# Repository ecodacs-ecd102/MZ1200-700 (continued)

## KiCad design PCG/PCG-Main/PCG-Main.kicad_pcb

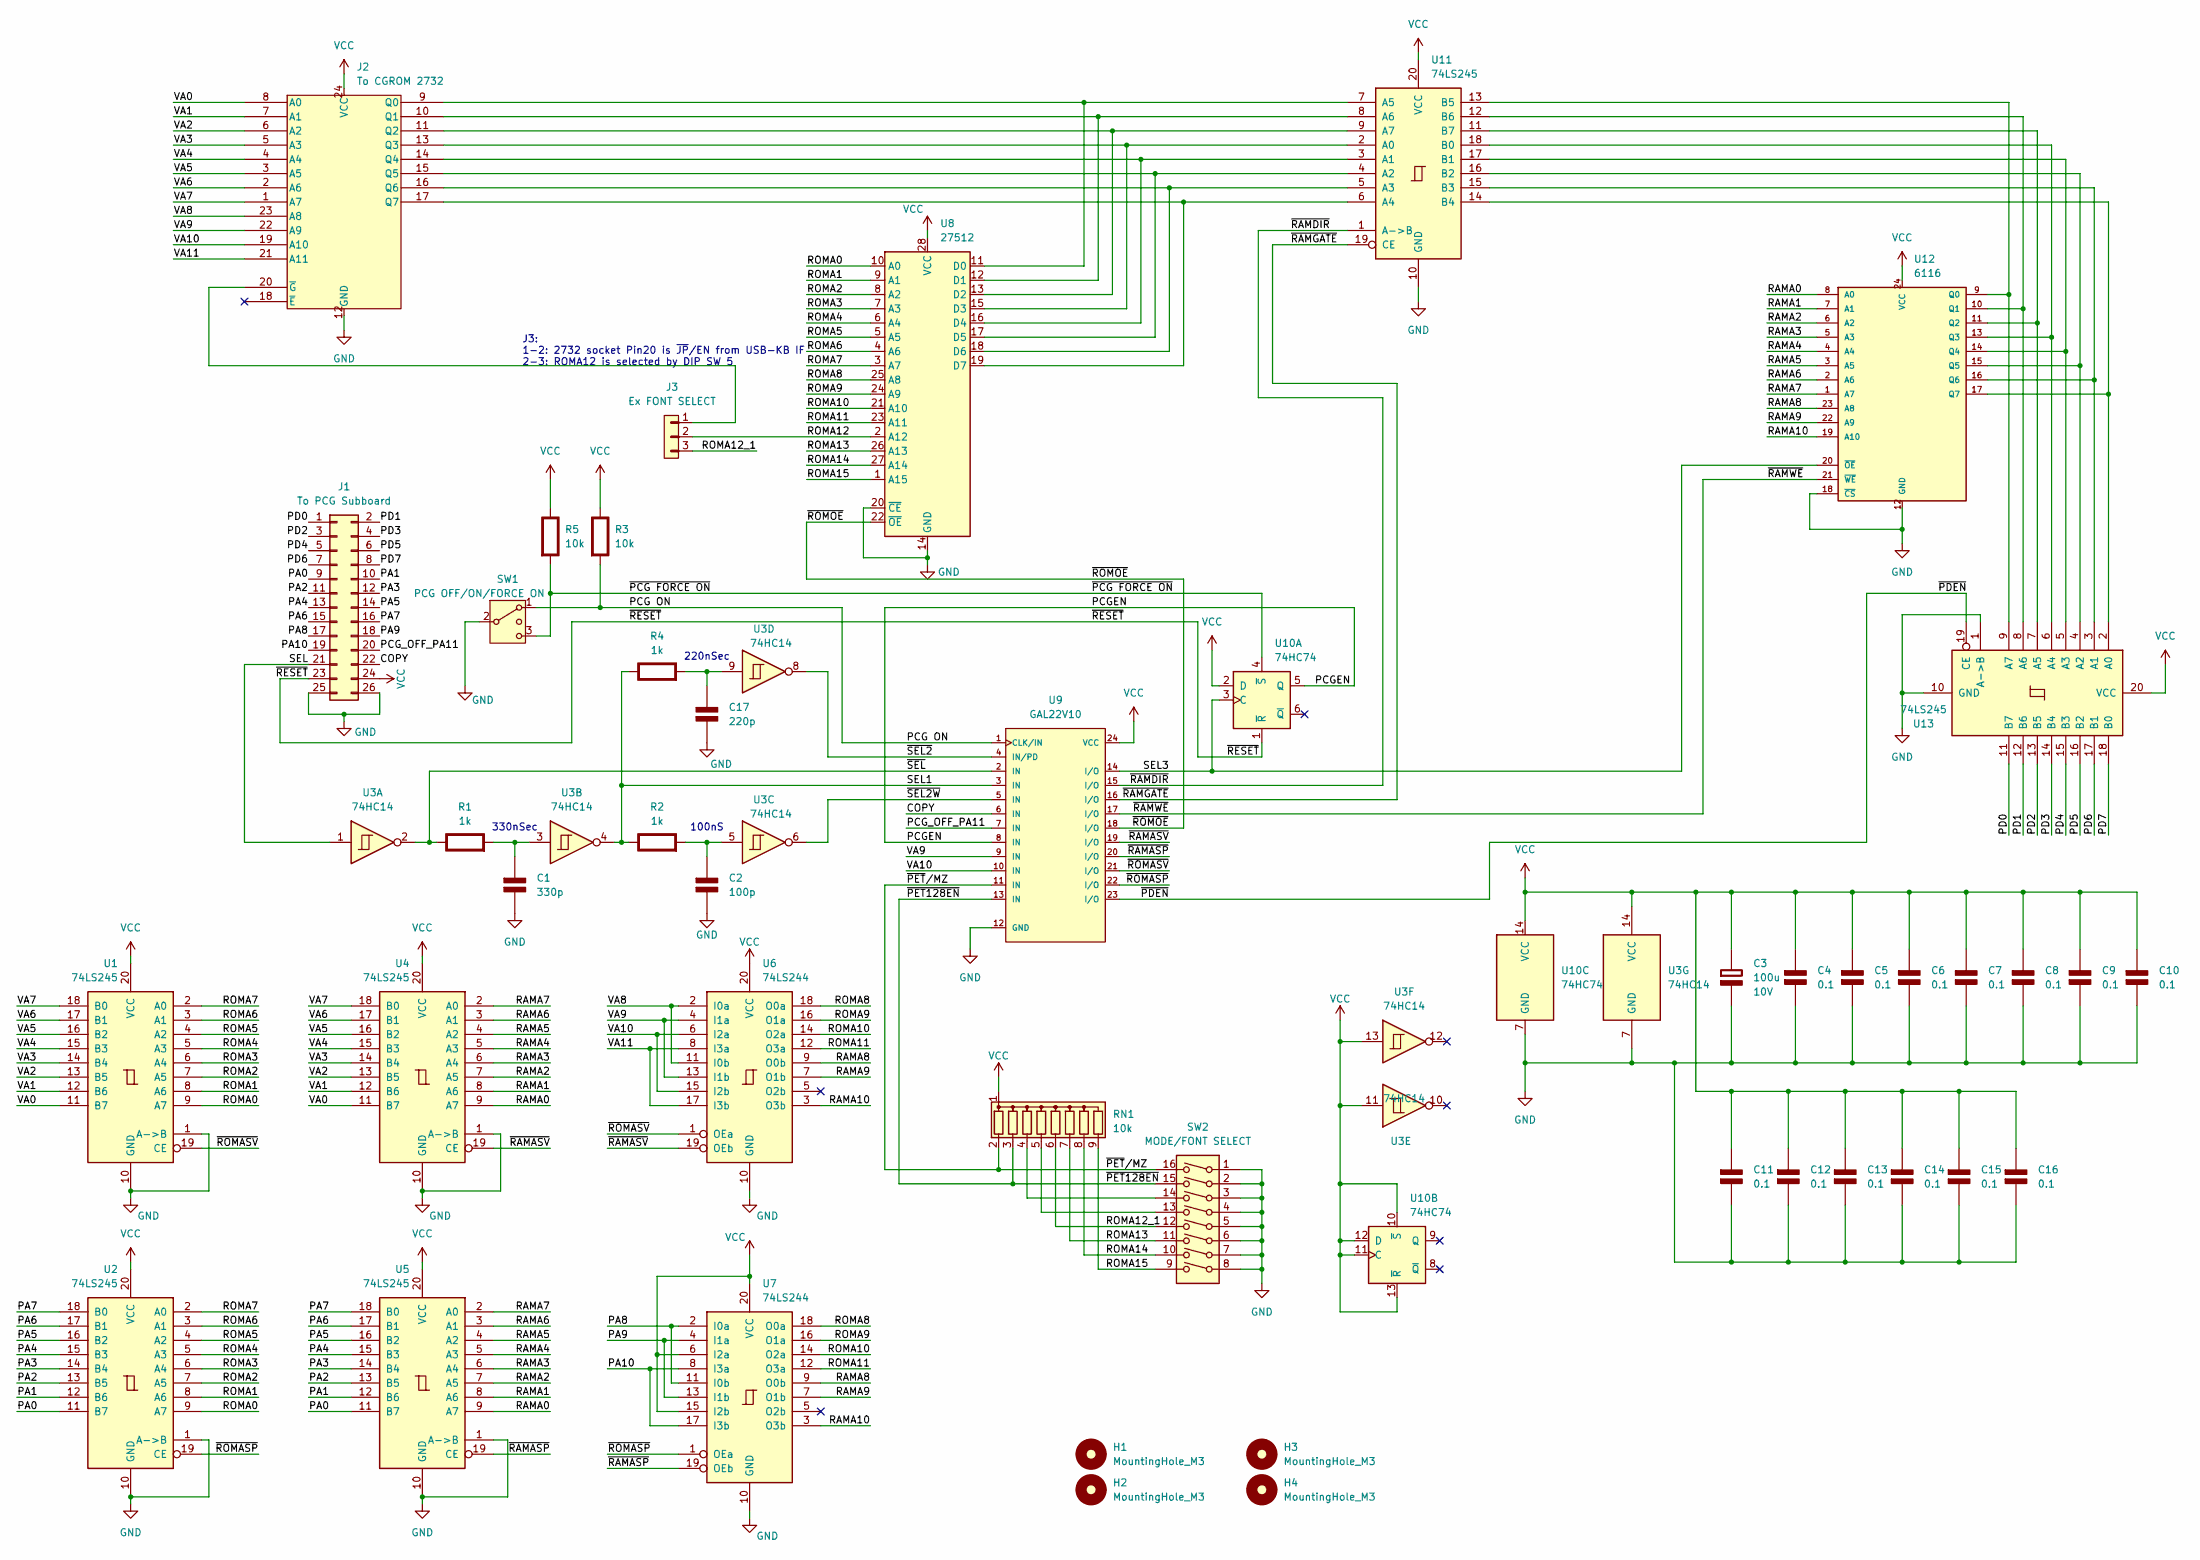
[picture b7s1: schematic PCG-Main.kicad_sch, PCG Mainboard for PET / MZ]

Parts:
C1: 330p; LargePad_R_Axial_DIN0204_L3.6mm_D1.6mm_P2.54mm_Vertical; Rating V
C2: 100p; LargePad_R_Axial_DIN0204_L3.6mm_D1.6mm_P2.54mm_Vertical; Rating V
C3: 100u; CP_Radial_D8.0mm_P3.50mm; Rating 10V
C4, C5, C6, C7, C8, C9, C10, C11, C12, C13, C14, C15, C16: 0.1; LargePad_R_Axial_DIN0204_L3.6mm_D1.6mm_P2.54mm_Vertical; Rating V
C17: 220p; LargePad_R_Axial_DIN0204_L3.6mm_D1.6mm_P2.54mm_Vertical; Rating V
H1, H2, H3, H4: MountingHole_M3; MountingHole_3.2mm_M3
J1: To PCG Subboard; PinSocket_2x13_P2.54mm_Vertical_LargePad
J2: To CGROM 2732; DIP-24_W15.24mm_Socket_LongPads
J3: Ex FONT SELECT; PinHeader_1x03_P2.54mm_Vertical
R1, R2, R4: 1k; LargePad_R_Axial_DIN0207_L6.3mm_D2.5mm_P7.62mm_Horizontal; Rating W
R3, R5: 10k; LargePad_R_Axial_DIN0207_L6.3mm_D2.5mm_P7.62mm_Horizontal; Rating W
RN1: 10k; R_Array_SIP9
SW1: PCG OFF/ON/FORCE ON; PinHeader_1x03_P2.54mm_Vertical
SW2: MODE/FONT SELECT; DIP-16_W7.62mm_Socket_LongPads
U1, U2, U4, U5, U11, U13: 74LS245; DIP-20_W7.62mm_Socket_LongPads
U3: 74HC14; DIP-14_W7.62mm_Socket_LongPads
U6, U7: 74LS244; DIP-20_W7.62mm_Socket_LongPads
U8: 27512; DIP-28_W15.24mm_Socket_LongPads
U9: GAL22V10; DIP-24_W7.62mm_Socket_LongPads
U10: 74HC74; DIP-14_W7.62mm_Socket_LongPads
U12: 6116; DIP-24_W15.24mm_Socket_LongPads

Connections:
/COPY: J1.22, U9.6 (IN)
/PA0: J1.9, U2.11 (B7), U5.11 (B7)
/PA1: J1.10, U2.12 (B6), U5.12 (B6)
/PA2: J1.11, U2.13 (B5), U5.13 (B5)
/PA3: J1.12, U2.14 (B4), U5.14 (B4)
/PA4: J1.13, U2.15 (B3), U5.15 (B3)
/PA5: J1.14, U2.16 (B2), U5.16 (B2)
/PA6: J1.15, U2.17 (B1), U5.17 (B1)
/PA7: J1.16, U2.18 (B0), U5.18 (B0)
/PA8: J1.17, U7.2 (I0a), U7.11 (I0b)
/PA9: J1.18, U7.4 (I1a), U7.13 (I1b)
/PA10: J1.19, U7.8 (I3a), U7.17 (I3b)
/PCG ON: R3.2 (-), SW1.1, U9.1 (CLK/IN)
/PCGEN: U9.8 (IN), U10.5 (Q)
/PCG_OFF_PA11: J1.20, U9.7 (IN)
/PD0: J1.1, U13.11 (B7)
/PD1: J1.2, U13.12 (B6)
/PD2: J1.3, U13.13 (B5)
/PD3: J1.4, U13.14 (B4)
/PD4: J1.5, U13.15 (B3)
/PD5: J1.6, U13.16 (B2)
/PD6: J1.7, U13.17 (B1)
/PD7: J1.8, U13.18 (B0)
/RAMA0: U4.9 (A7), U5.9 (A7), U12.8 (A0)
/RAMA1: U4.8 (A6), U5.8 (A6), U12.7 (A1)
/RAMA2: U4.7 (A5), U5.7 (A5), U12.6 (A2)
/RAMA3: U4.6 (A4), U5.6 (A4), U12.5 (A3)
/RAMA4: U4.5 (A3), U5.5 (A3), U12.4 (A4)
/RAMA5: U4.4 (A2), U5.4 (A2), U12.3 (A5)
/RAMA6: U4.3 (A1), U5.3 (A1), U12.2 (A6)
/RAMA7: U4.2 (A0), U5.2 (A0), U12.1 (A7)
/RAMA8: U6.9 (O0b), U7.9 (O0b), U12.23 (A8)
/RAMA9: U6.7 (O1b), U7.7 (O1b), U12.22 (A9)
/RAMA10: U6.3 (O3b), U7.3 (O3b), U12.19 (A10)
/ROMA0: U1.9 (A7), U2.9 (A7), U8.10 (A0)
/ROMA1: U1.8 (A6), U2.8 (A6), U8.9 (A1)
/ROMA2: U1.7 (A5), U2.7 (A5), U8.8 (A2)
/ROMA3: U1.6 (A4), U2.6 (A4), U8.7 (A3)
/ROMA4: U1.5 (A3), U2.5 (A3), U8.6 (A4)
/ROMA5: U1.4 (A2), U2.4 (A2), U8.5 (A5)
/ROMA6: U1.3 (A1), U2.3 (A1), U8.4 (A6)
/ROMA7: U1.2 (A0), U2.2 (A0), U8.3 (A7)
/ROMA8: U6.18 (O0a), U7.18 (O0a), U8.25 (A8)
/ROMA9: U6.16 (O1a), U7.16 (O1a), U8.24 (A9)
/ROMA10: U6.14 (O2a), U7.14 (O2a), U8.21 (A10)
/ROMA11: U6.12 (O3a), U7.12 (O3a), U8.23 (A11)
/ROMA12: J3.2, U8.2 (A12)
/ROMA12_1: J3.3, RN1.6 (R5), SW2.12
/ROMA13: RN1.7 (R6), SW2.11, U8.26 (A13)
/ROMA14: RN1.8 (R7), SW2.10, U8.27 (A14)
/ROMA15: RN1.9 (R8), SW2.9, U8.1 (A15)
/SEL: J1.21, U3.1
/SEL1: R2.1 (+), R4.1 (+), U3.4, U9.3 (IN)
/SEL3: U9.14 (I/O), U10.3 (C), U12.20 (~OE)
/VA0: J2.8 (A0), U1.11 (B7), U4.11 (B7)
/VA1: J2.7 (A1), U1.12 (B6), U4.12 (B6)
/VA2: J2.6 (A2), U1.13 (B5), U4.13 (B5)
/VA3: J2.5 (A3), U1.14 (B4), U4.14 (B4)
/VA4: J2.4 (A4), U1.15 (B3), U4.15 (B3)
/VA5: J2.3 (A5), U1.16 (B2), U4.16 (B2)
/VA6: J2.2 (A6), U1.17 (B1), U4.17 (B1)
/VA7: J2.1 (A7), U1.18 (B0), U4.18 (B0)
/VA8: J2.23 (A8), U6.2 (I0a), U6.11 (I0b)
/VA9: J2.22 (A9), U6.4 (I1a), U6.13 (I1b), U9.9 (IN)
/VA10: J2.19 (A10), U6.6 (I2a), U6.15 (I2b), U9.10 (IN)
/VA11: J2.21 (A11), U6.8 (I3a), U6.17 (I3b)
/~PCG FORCE ON: R5.2 (-), SW1.3 (4), U10.4 (~S)
/~PDEN: U9.23 (I/O), U13.19 (CE)
/~PET128EN: RN1.3 (R2), SW2.15, U9.13 (IN)
/~PET/MZ: RN1.2 (R1), SW2.16, U9.11 (IN)
/~RAMASP: U5.19 (CE), U7.19 (OEb), U9.20 (I/O)
/~RAMASV: U4.19 (CE), U6.19 (OEb), U9.19 (I/O)
/~RAMDIR: U9.15 (I/O), U11.1 (A->B)
/~RAMGATE: U9.16 (I/O), U11.19 (CE)
/~RAMWE: U9.17 (I/O), U12.21 (~WE)
/~RESET: J1.23, U10.1 (~R)
/~ROMASP: U2.19 (CE), U7.1 (OEa), U9.22 (I/O)
/~ROMASV: U1.19 (CE), U6.1 (OEa), U9.21 (I/O)
/~ROMOE: U8.22 (~OE), U9.18 (I/O)
/~SEL2W: U3.6, U9.5 (IN)
/~SEL2: U3.8, U9.4 (IN/PD)
/~SEL: R1.1 (+), U3.2, U9.2 (IN)
GND: C1.2 (-), C2.2 (-), C3.2 (-), C4.2 (-), C5.2 (-), C6.2 (-), C7.2 (-), C8.2 (-), C9.2 (-), C10.2 (-), C11.2 (-), C12.2 (-), C13.2 (-), C14.2 (-), C15.2 (-), C16.2 (-), C17.2 (-), J1.25, J1.26, J2.12 (GND), SW1.2 (3), SW2.1, SW2.2, SW2.3, SW2.4, SW2.5, SW2.6, SW2.7, SW2.8, U1.1 (A->B), U1.10 (GND), U2.1 (A->B), U2.10 (GND), U3.7 (GND), U4.1 (A->B), U4.10 (GND), U5.1 (A->B), U5.10 (GND), U6.10 (GND), U7.10 (GND), U8.14 (GND), U8.20 (~CE), U9.12 (GND), U10.7 (GND), U11.10 (GND), U12.12 (GND), U12.18 (~CS), U13.1 (A->B), U13.10 (GND)
unnamed: C1.1 (+), R1.2 (-), U3.3
unnamed: C2.1 (+), R2.2 (-), U3.5
unnamed: C17.1 (+), R4.2 (-), U3.9
unnamed: J2.9 (Q0), U8.11 (D0), U11.7 (A5)
unnamed: J2.10 (Q1), U8.12 (D1), U11.8 (A6)
unnamed: J2.11 (Q2), U8.13 (D2), U11.9 (A7)
unnamed: J2.13 (Q3), U8.15 (D3), U11.2 (A0)
unnamed: J2.14 (Q4), U8.16 (D4), U11.3 (A1)
unnamed: J2.15 (Q5), U8.17 (D5), U11.4 (A2)
unnamed: J2.16 (Q6), U8.18 (D6), U11.5 (A3)
unnamed: J2.17 (Q7), U8.19 (D7), U11.6 (A4)
unnamed: J2.20 (~G), J3.1
unnamed: RN1.4 (R3), SW2.14
unnamed: RN1.5 (R4), SW2.13
unnamed: U11.18 (B0), U12.13 (Q3), U13.6 (A4)
unnamed: U11.17 (B1), U12.14 (Q4), U13.5 (A3)
unnamed: U11.16 (B2), U12.15 (Q5), U13.4 (A2)
unnamed: U11.15 (B3), U12.16 (Q6), U13.3 (A1)
unnamed: U11.14 (B4), U12.17 (Q7), U13.2 (A0)
unnamed: U11.13 (B5), U12.9 (Q0), U13.9 (A7)
unnamed: U11.12 (B6), U12.10 (Q1), U13.8 (A6)
unnamed: U11.11 (B7), U12.11 (Q2), U13.7 (A5)
VCC: C3.1 (+), C4.1 (+), C5.1 (+), C6.1 (+), C7.1 (+), C8.1 (+), C9.1 (+), C10.1 (+), C11.1 (+), C12.1 (+), C13.1 (+), C14.1 (+), C15.1 (+), C16.1 (+), J1.24, J2.24 (VCC), R3.1 (+), R5.1 (+), RN1.1 (common), U1.20 (VCC), U2.20 (VCC), U3.11, U3.13, U3.14 (VCC), U4.20 (VCC), U5.20 (VCC), U6.20 (VCC), U7.6 (I2a), U7.15 (I2b), U7.20 (VCC), U8.28 (VCC), U9.24 (VCC), U10.2 (D), U10.10 (~S), U10.11 (C), U10.12 (D), U10.13 (~R), U10.14 (VCC), U11.20 (VCC), U12.24 (VCC), U13.20 (VCC)

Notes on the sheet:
100nS
J3: 1-2: 2732 socket Pin20 is ~{JP}/EN from USB-KB IF 2-3: ROMA12 is selected by DIP SW 5
220nSec
330nSec

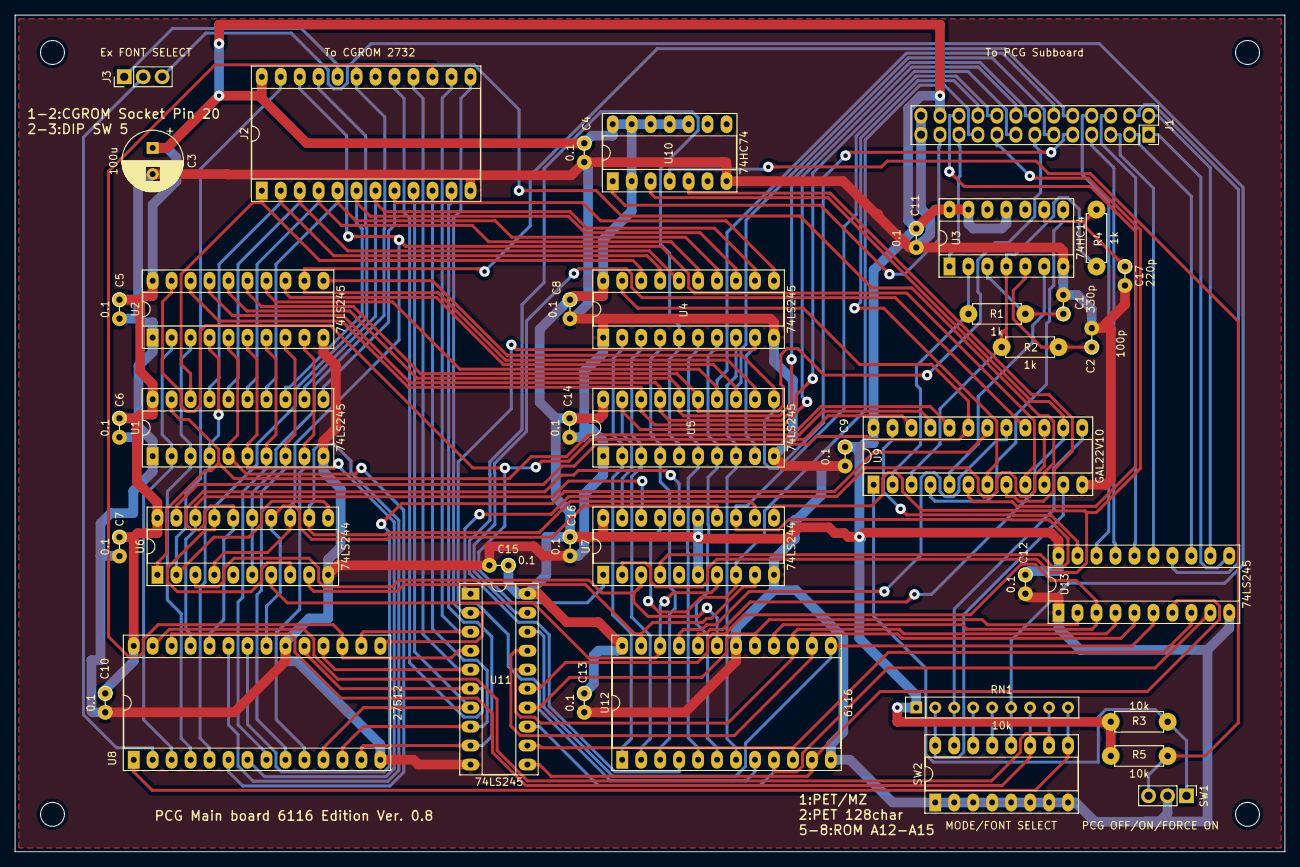
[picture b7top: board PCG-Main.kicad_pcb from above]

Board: 2 copper layers, 170.0 x 112.0 mm, 45 parts (0 on the bottom side), 106 nets.

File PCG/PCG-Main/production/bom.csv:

Designator,Footprint,Quantity,Value,LCSC Part #
C1,LargePad_R_Axial_DIN0204_L3.6mm_D1.6mm_P2.54mm_Vertical,1,330p,
"C10, C11, C12, C13, C14, C15, C16, C4, C5, C6, C7, C8, C9",LargePad_R_Axial_DIN0204_L3.6mm_D1.6mm_P2.54mm_Vertical,13,0.1,
C17,LargePad_R_Axial_DIN0204_L3.6mm_D1.6mm_P2.54mm_Vertical,1,220p,
C2,LargePad_R_Axial_DIN0204_L3.6mm_D1.6mm_P2.54mm_Vertical,1,100p,
C3,CP_Radial_D8.0mm_P3.50mm,1,100u,
"H1, H2, H3, H4",MountingHole_3.2mm_M3,4,MountingHole_M3,
J1,PinSocket_2x13_P2.54mm_Vertical_LargePad,1,To PCG Subboard,
J2,DIP-24_W15.24mm_Socket_LongPads,1,To CGROM 2732,
J3,PinHeader_1x03_P2.54mm_Vertical,1,Ex FONT SELECT,
"R1, R2, R4",LargePad_R_Axial_DIN0207_L6.3mm_D2.5mm_P7.62mm_Horizontal,3,1k,
"R3, R5",LargePad_R_Axial_DIN0207_L6.3mm_D2.5mm_P7.62mm_Horizontal,2,10k,
RN1,R_Array_SIP9,1,10k,
SW1,PinHeader_1x03_P2.54mm_Vertical,1,PCG OFF/ON/FORCE ON,
SW2,DIP-16_W7.62mm_Socket_LongPads,1,MODE/FONT SELECT,
"U1, U11, U13, U2, U4, U5",DIP-20_W7.62mm_Socket_LongPads,6,74HC245,
U10,DIP-14_W7.62mm_Socket_LongPads,1,74HC74,
U12,DIP-24_W15.24mm_Socket_LongPads,1,6116,
U3,DIP-14_W7.62mm_Socket_LongPads,1,74HC14,
"U6, U7",DIP-20_W7.62mm_Socket_LongPads,2,74HC244,
U8,DIP-28_W15.24mm_Socket_LongPads,1,27512,
U9,DIP-24_W7.62mm_Socket_LongPads,1,GAL22V10,

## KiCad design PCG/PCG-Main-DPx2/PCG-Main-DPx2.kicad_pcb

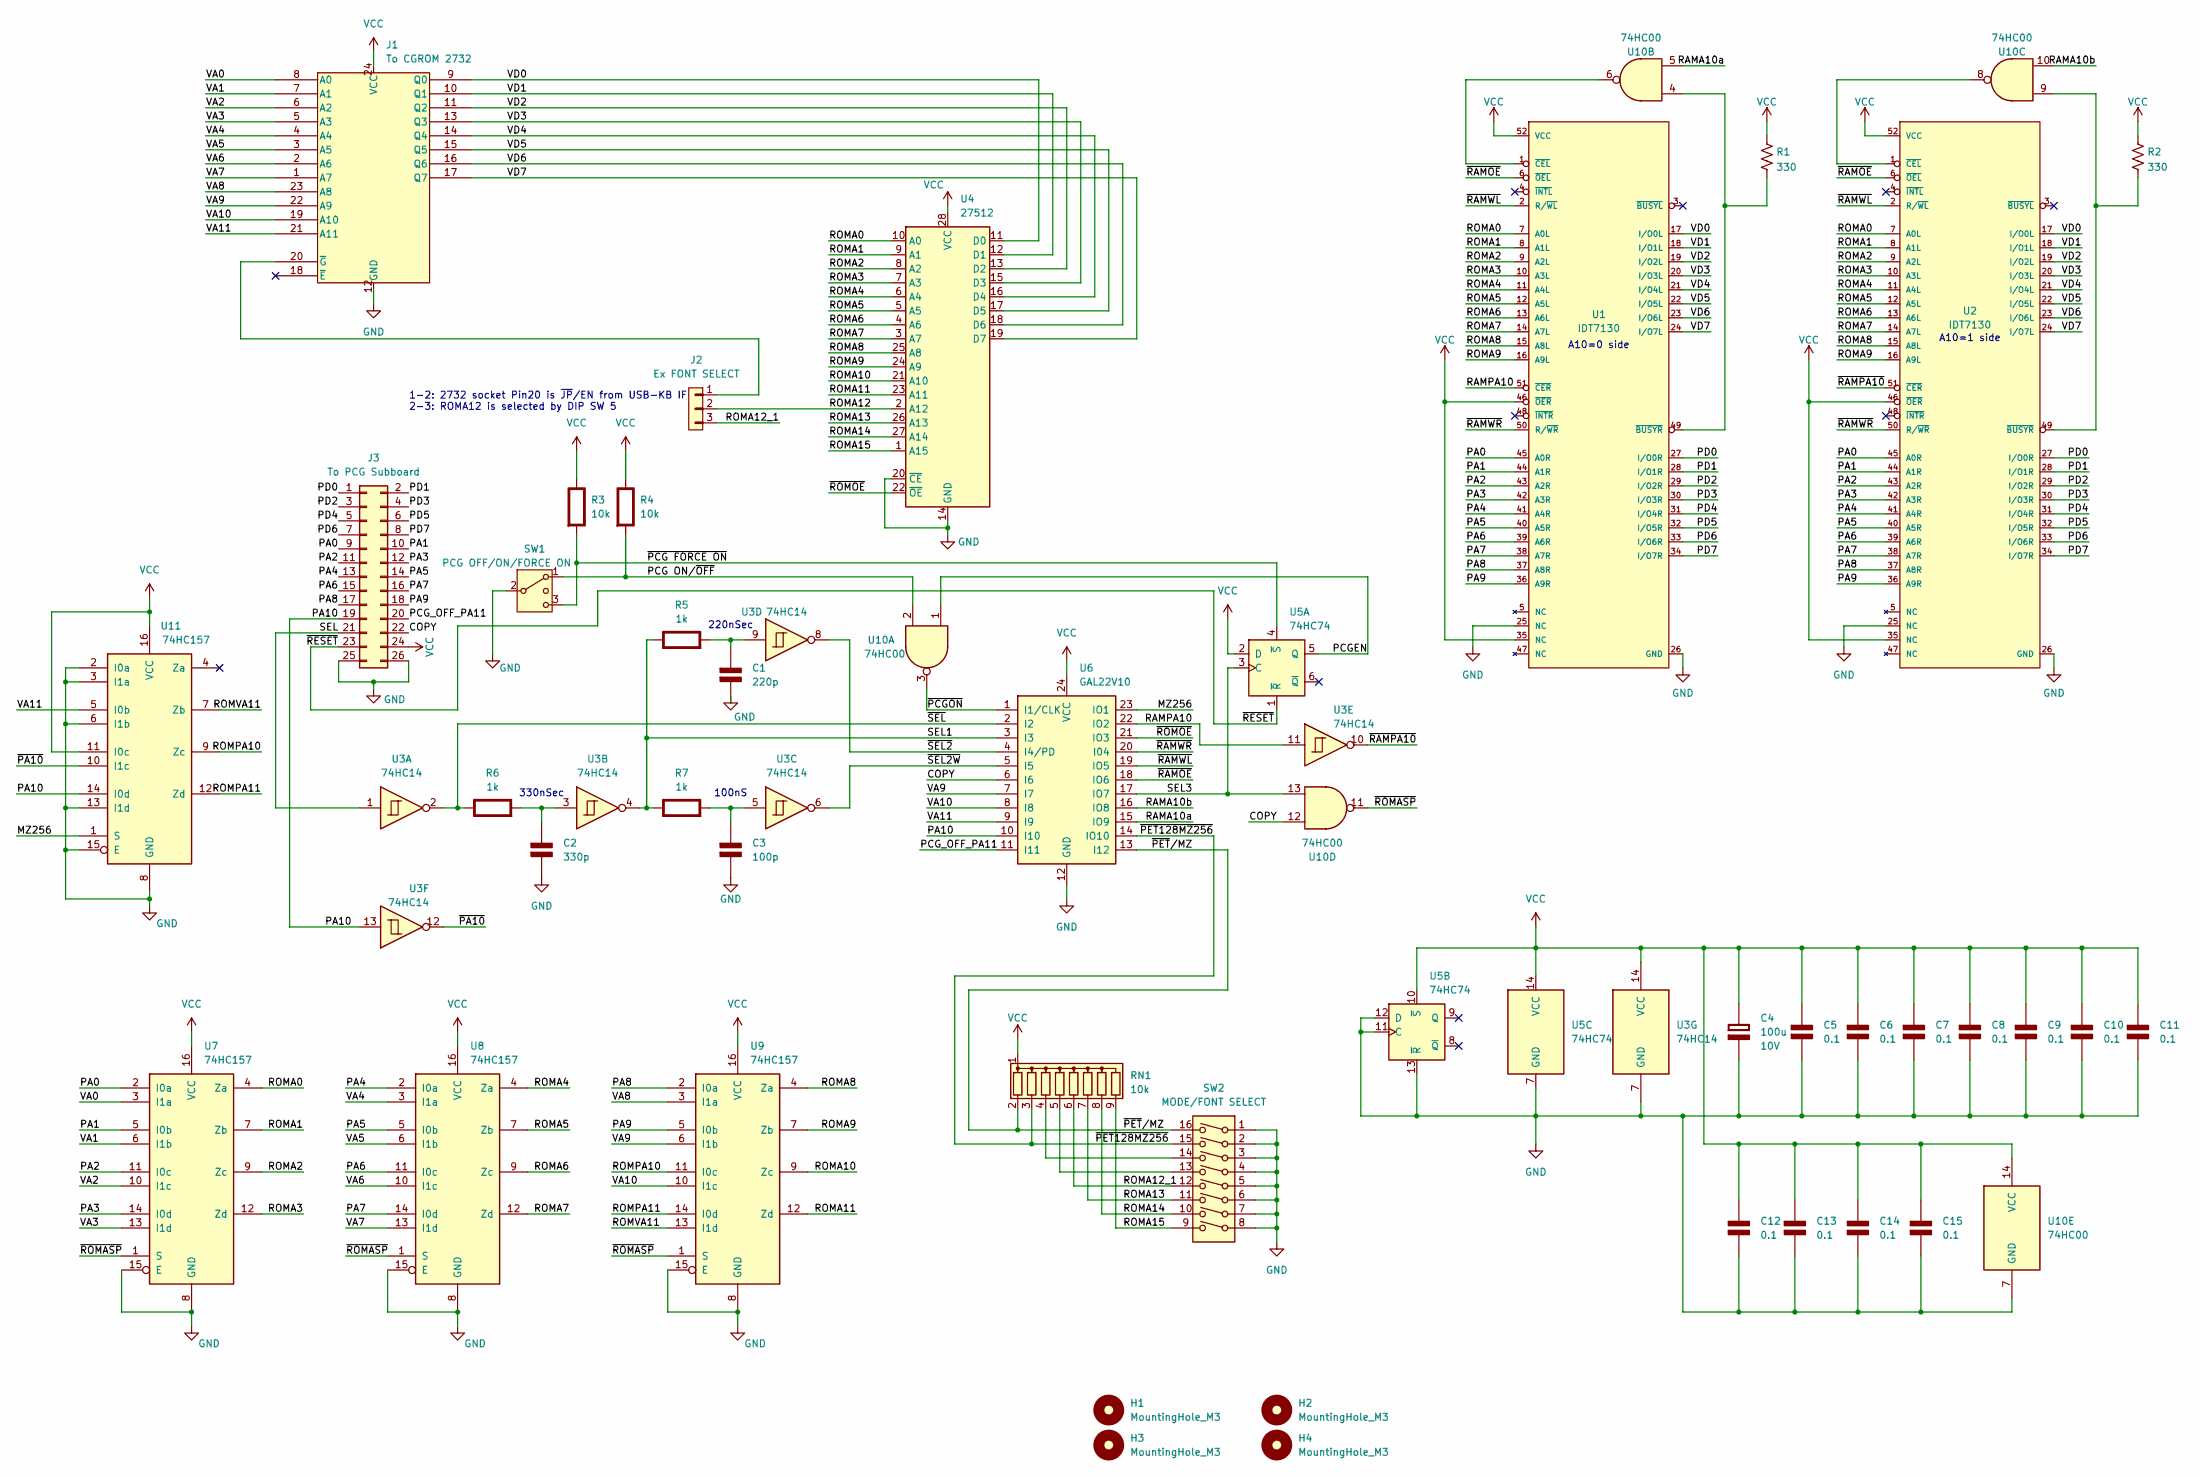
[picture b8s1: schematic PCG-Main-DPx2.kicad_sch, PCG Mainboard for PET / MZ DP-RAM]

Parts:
C1: 220p; LargePad_R_Axial_DIN0204_L3.6mm_D1.6mm_P2.54mm_Vertical; Rating V
C2: 330p; LargePad_R_Axial_DIN0204_L3.6mm_D1.6mm_P2.54mm_Vertical; Rating V
C3: 100p; LargePad_R_Axial_DIN0204_L3.6mm_D1.6mm_P2.54mm_Vertical; Rating V
C4: 100u; CP_Radial_D8.0mm_P3.50mm; Rating 10V
C5, C6, C7, C8, C9, C10, C11, C12, C13, C14, C15: 0.1; LargePad_R_Axial_DIN0204_L3.6mm_D1.6mm_P2.54mm_Vertical; Rating V
H1, H2, H3, H4: MountingHole_M3; MountingHole_3.2mm_M3
J1: To CGROM 2732; DIP-24_W15.24mm_Socket_LongPads
J2: Ex FONT SELECT; PinHeader_1x03_P2.54mm_Vertical
J3: To PCG Subboard; PinSocket_2x13_P2.54mm_Vertical_LargePad
R1, R2: 330; R_Axial_DIN0207_L6.3mm_D2.5mm_P10.16mm_Horizontal
R3, R4: 10k; LargePad_R_Axial_DIN0207_L6.3mm_D2.5mm_P7.62mm_Horizontal; Rating W
R5, R6, R7: 1k; LargePad_R_Axial_DIN0207_L6.3mm_D2.5mm_P7.62mm_Horizontal; Rating W
RN1: 10k; R_Array_SIP9
SW1: PCG OFF/ON/FORCE ON; PinHeader_1x03_P2.54mm_Vertical
SW2: MODE/FONT SELECT; DIP-16_W7.62mm_Socket_LongPads
U1, U2: IDT7130; PLCC-52_THT-Socket; voltage 5.0V; mouser part number 972-7130LA35J; digikey description SRAM - Dual Port, Asynchronous Memory I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
U3: 74HC14; DIP-14_W7.62mm_Socket_LongPads
U4: 27512; DIP-28_W15.24mm_Socket_LongPads
U5: 74HC74; DIP-14_W7.62mm_Socket_LongPads
U6: GAL22V10; DIP-24_W7.62mm_Socket_LongPads
U7, U8, U9, U11: 74HC157; DIP-16_W7.62mm_Socket_LongPads
U10: 74HC00; DIP-14_W7.62mm_Socket_LongPads

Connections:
/COPY: J3.22, U6.6 (I6), U10.12
/MZ256: U6.23 (IO1), U11.1 (S)
/PA0: J3.9, U1.45 (A0R), U2.45 (A0R), U7.2 (I0a)
/PA1: J3.10, U1.44 (A1R), U2.44 (A1R), U7.5 (I0b)
/PA2: J3.11, U1.43 (A2R), U2.43 (A2R), U7.11 (I0c)
/PA3: J3.12, U1.42 (A3R), U2.42 (A3R), U7.14 (I0d)
/PA4: J3.13, U1.41 (A4R), U2.41 (A4R), U8.2 (I0a)
/PA5: J3.14, U1.40 (A5R), U2.40 (A5R), U8.5 (I0b)
/PA6: J3.15, U1.39 (A6R), U2.39 (A6R), U8.11 (I0c)
/PA7: J3.16, U1.38 (A7R), U2.38 (A7R), U8.14 (I0d)
/PA8: J3.17, U1.37 (A8R), U2.37 (A8R), U9.2 (I0a)
/PA9: J3.18, U1.36 (A9R), U2.36 (A9R), U9.5 (I0b)
/PA10: J3.19, U3.13, U6.10 (I10), U11.14 (I0d)
/PCG ON/~OFF: R4.2 (-), SW1.1, U10.2
/PCGEN: U5.5 (Q), U10.1
/PCG_OFF_PA11: J3.20, U6.11 (I11)
/PD0: J3.1, U1.27 (I/O0R), U2.27 (I/O0R)
/PD1: J3.2, U1.28 (I/O1R), U2.28 (I/O1R)
/PD2: J3.3, U1.29 (I/O2R), U2.29 (I/O2R)
/PD3: J3.4, U1.30 (I/O3R), U2.30 (I/O3R)
/PD4: J3.5, U1.31 (I/O4R), U2.31 (I/O4R)
/PD5: J3.6, U1.32 (I/O5R), U2.32 (I/O5R)
/PD6: J3.7, U1.33 (I/O6R), U2.33 (I/O6R)
/PD7: J3.8, U1.34 (I/O7R), U2.34 (I/O7R)
/RAMA10a: U6.15 (IO9), U10.5
/RAMA10b: U6.16 (IO8), U10.10
/RAMPA10: U1.51 (~CER), U3.11, U6.22 (IO2)
/ROMA0: U1.7 (A0L), U2.7 (A0L), U4.10 (A0), U7.4 (Za)
/ROMA1: U1.8 (A1L), U2.8 (A1L), U4.9 (A1), U7.7 (Zb)
/ROMA2: U1.9 (A2L), U2.9 (A2L), U4.8 (A2), U7.9 (Zc)
/ROMA3: U1.10 (A3L), U2.10 (A3L), U4.7 (A3), U7.12 (Zd)
/ROMA4: U1.11 (A4L), U2.11 (A4L), U4.6 (A4), U8.4 (Za)
/ROMA5: U1.12 (A5L), U2.12 (A5L), U4.5 (A5), U8.7 (Zb)
/ROMA6: U1.13 (A6L), U2.13 (A6L), U4.4 (A6), U8.9 (Zc)
/ROMA7: U1.14 (A7L), U2.14 (A7L), U4.3 (A7), U8.12 (Zd)
/ROMA8: U1.15 (A8L), U2.15 (A8L), U4.25 (A8), U9.4 (Za)
/ROMA9: U1.16 (A9L), U2.16 (A9L), U4.24 (A9), U9.7 (Zb)
/ROMA10: U4.21 (A10), U9.9 (Zc)
/ROMA11: U4.23 (A11), U9.12 (Zd)
/ROMA12: J2.2, U4.2 (A12)
/ROMA12_1: J2.3, RN1.6 (R5), SW2.12
/ROMA13: RN1.7 (R6), SW2.11, U4.26 (A13)
/ROMA14: RN1.8 (R7), SW2.10, U4.27 (A14)
/ROMA15: RN1.9 (R8), SW2.9, U4.1 (A15)
/ROMPA10: U9.11 (I0c), U11.9 (Zc)
/ROMPA11: U9.14 (I0d), U11.12 (Zd)
/ROMVA11: U9.13 (I1d), U11.7 (Zb)
/SEL: J3.21, U3.1
/SEL1: R5.1 (+), R7.1 (+), U3.4, U6.3 (I3)
/SEL3: U5.3 (C), U6.17 (IO7), U10.13
/VA0: J1.8 (A0), U7.3 (I1a)
/VA1: J1.7 (A1), U7.6 (I1b)
/VA2: J1.6 (A2), U7.10 (I1c)
/VA3: J1.5 (A3), U7.13 (I1d)
/VA4: J1.4 (A4), U8.3 (I1a)
/VA5: J1.3 (A5), U8.6 (I1b)
/VA6: J1.2 (A6), U8.10 (I1c)
/VA7: J1.1 (A7), U8.13 (I1d)
/VA8: J1.23 (A8), U9.3 (I1a)
/VA9: J1.22 (A9), U6.7 (I7), U9.6 (I1b)
/VA10: J1.19 (A10), U6.8 (I8), U9.10 (I1c)
/VA11: J1.21 (A11), U6.9 (I9), U11.5 (I0b)
/VD0: J1.9 (Q0), U1.17 (I/O0L), U2.17 (I/O0L), U4.11 (D0)
/VD1: J1.10 (Q1), U1.18 (I/O1L), U2.18 (I/O1L), U4.12 (D1)
/VD2: J1.11 (Q2), U1.19 (I/O2L), U2.19 (I/O2L), U4.13 (D2)
/VD3: J1.13 (Q3), U1.20 (I/O3L), U2.20 (I/O3L), U4.15 (D3)
/VD4: J1.14 (Q4), U1.21 (I/O4L), U2.21 (I/O4L), U4.16 (D4)
/VD5: J1.15 (Q5), U1.22 (I/O5L), U2.22 (I/O5L), U4.17 (D5)
/VD6: J1.16 (Q6), U1.23 (I/O6L), U2.23 (I/O6L), U4.18 (D6)
/VD7: J1.17 (Q7), U1.24 (I/O7L), U2.24 (I/O7L), U4.19 (D7)
/~PA10: U3.12, U11.10 (I1c)
/~PCG FORCE ON: R3.2 (-), SW1.3 (4), U5.4 (~S)
/~PCGON: U6.1 (I1/CLK), U10.3
/~PET128MZ256: RN1.3 (R2), SW2.15, U6.14 (IO10)
/~PET/MZ: RN1.2 (R1), SW2.16, U6.13 (I12)
/~RAMOE: U1.6 (~OEL), U2.6 (~OEL), U6.18 (IO6)
/~RAMPA10: U2.51 (~CER), U3.10
/~RAMWL: U1.2 (R/~WL), U2.2 (R/~WL), U6.19 (IO5)
/~RAMWR: U1.50 (R/~WR), U2.50 (R/~WR), U6.20 (I04)
/~RESET: J3.23, U5.1 (~R)
/~ROMASP: U7.1 (S), U8.1 (S), U9.1 (S), U10.11
/~ROMOE: U4.22 (~OE), U6.21 (IO3)
/~SEL2W: U3.6, U6.5 (I5)
/~SEL2: U3.8, U6.4 (I4/PD)
/~SEL: R6.1 (+), U3.2, U6.2 (I2)
GND: C1.2 (-), C2.2 (-), C3.2 (-), C4.2 (-), C5.2 (-), C6.2 (-), C7.2 (-), C8.2 (-), C9.2 (-), C10.2 (-), C11.2 (-), C12.2 (-), C13.2 (-), C14.2 (-), C15.2 (-), J1.12 (GND), J3.25, J3.26, SW1.2 (3), SW2.1, SW2.2, SW2.3, SW2.4, SW2.5, SW2.6, SW2.7, SW2.8, U1.25 (NC), U1.26 (GND), U2.25 (NC), U2.26 (GND), U3.7 (GND), U4.14 (GND), U4.20 (~CE), U5.7 (GND), U5.11 (C), U5.12 (D), U5.13 (~R), U6.12 (GND), U7.8 (GND), U7.15 (E), U8.8 (GND), U8.15 (E), U9.8 (GND), U9.15 (E), U10.7 (GND), U11.2 (I0a), U11.3 (I1a), U11.6 (I1b), U11.8 (GND), U11.13 (I1d), U11.15 (E)
unnamed: C1.1 (+), R5.2 (-), U3.9
unnamed: C2.1 (+), R6.2 (-), U3.3
unnamed: C3.1 (+), R7.2 (-), U3.5
unnamed: J1.20 (~G), J2.1
unnamed: RN1.4 (R3), SW2.14
unnamed: RN1.5 (R4), SW2.13
unnamed: R1.2, U1.49 (~BUSYR), U10.4
unnamed: U1.1 (~CEL), U10.6
unnamed: R2.2, U2.49 (~BUSYR), U10.9
unnamed: U2.1 (~CEL), U10.8
VCC: C4.1 (+), C5.1 (+), C6.1 (+), C7.1 (+), C8.1 (+), C9.1 (+), C10.1 (+), C11.1 (+), C12.1 (+), C13.1 (+), C14.1 (+), C15.1 (+), J1.24 (VCC), J3.24, R1.1, R2.1, R3.1 (+), R4.1 (+), RN1.1 (common), U1.35 (NC), U1.46 (~OER), U1.52 (VCC), U2.35 (NC), U2.46 (~OER), U2.52 (VCC), U3.14 (VCC), U4.28 (VCC), U5.2 (D), U5.10 (~S), U5.14 (VCC), U6.24 (VCC), U7.16 (VCC), U8.16 (VCC), U9.16 (VCC), U10.14 (VCC), U11.11 (I0c), U11.16 (VCC)

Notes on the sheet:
100nS
1-2: 2732 socket Pin20 is ~{JP}/EN from USB-KB IF 2-3: ROMA12 is selected by DIP SW 5
A10=1 side
A10=0 side
220nSec
330nSec

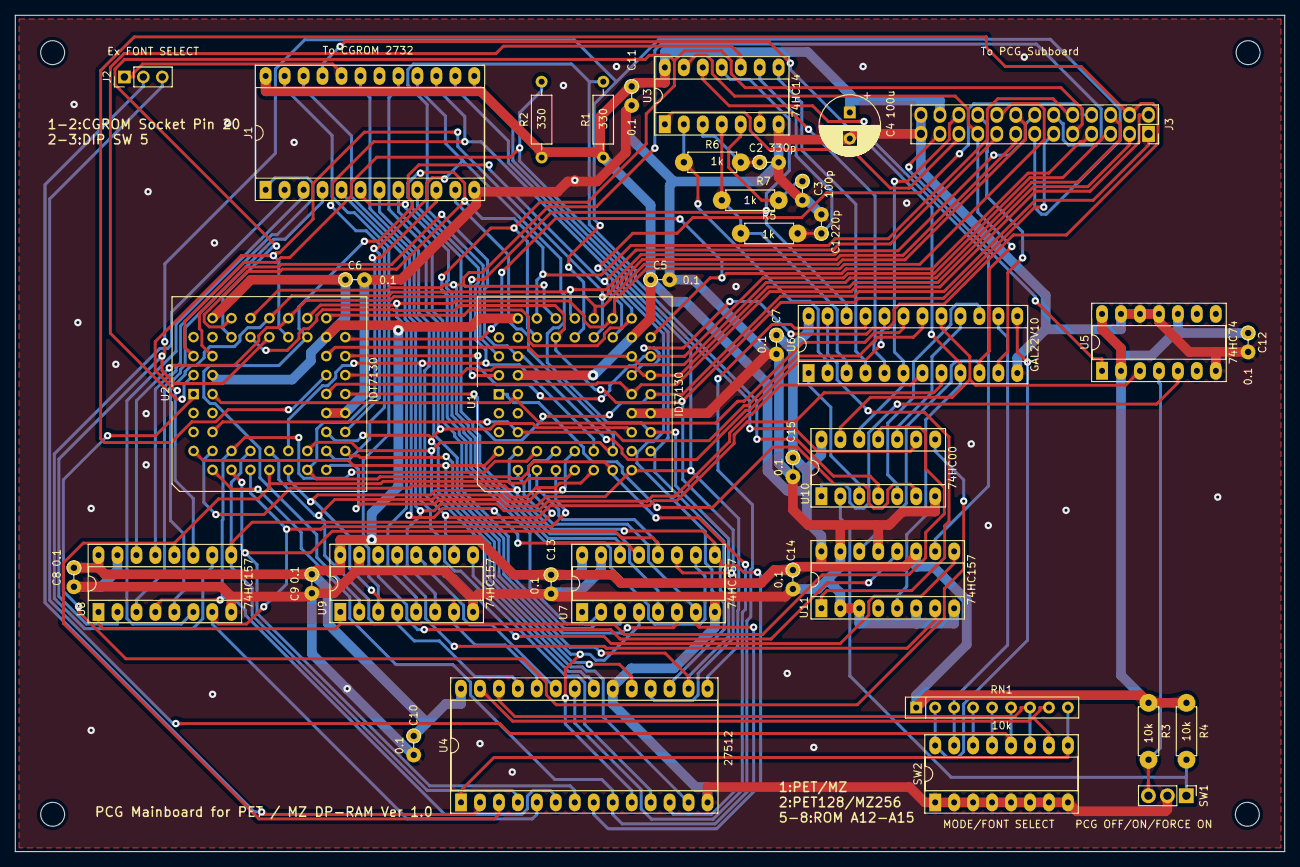
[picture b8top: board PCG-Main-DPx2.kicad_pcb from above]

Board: 2 copper layers, 170.0 x 112.0 mm, 43 parts (0 on the bottom side), 97 nets.

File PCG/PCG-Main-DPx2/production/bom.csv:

Designator,Footprint,Quantity,Value,LCSC Part #
C1,LargePad_R_Axial_DIN0204_L3.6mm_D1.6mm_P2.54mm_Vertical,1,220p,
"C10, C11, C12, C13, C14, C15, C5, C6, C7, C8, C9",LargePad_R_Axial_DIN0204_L3.6mm_D1.6mm_P2.54mm_Vertical,11,0.1,
C2,LargePad_R_Axial_DIN0204_L3.6mm_D1.6mm_P2.54mm_Vertical,1,330p,
C3,LargePad_R_Axial_DIN0204_L3.6mm_D1.6mm_P2.54mm_Vertical,1,100p,
C4,CP_Radial_D8.0mm_P3.50mm,1,100u,
"H1, H2, H3, H4",MountingHole_3.2mm_M3,4,MountingHole_M3,
J1,DIP-24_W15.24mm_Socket_LongPads,1,To CGROM 2732,
J2,PinHeader_1x03_P2.54mm_Vertical,1,Ex FONT SELECT,
J3,PinSocket_2x13_P2.54mm_Vertical_LargePad,1,To PCG Subboard,
"R1, R2",R_Axial_DIN0207_L6.3mm_D2.5mm_P10.16mm_Horizontal,2,330,
"R3, R4",LargePad_R_Axial_DIN0207_L6.3mm_D2.5mm_P7.62mm_Horizontal,2,10k,
"R5, R6, R7",LargePad_R_Axial_DIN0207_L6.3mm_D2.5mm_P7.62mm_Horizontal,3,1k,
RN1,R_Array_SIP9,1,10k,
SW1,PinHeader_1x03_P2.54mm_Vertical,1,PCG OFF/ON/FORCE ON,
SW2,DIP-16_W7.62mm_Socket_LongPads,1,MODE/FONT SELECT,
"U1, U2",PLCC-52_THT-Socket,2,IDT7130,
U10,DIP-14_W7.62mm_Socket_LongPads,1,74HC00,
"U11, U7, U8, U9",DIP-16_W7.62mm_Socket_LongPads,4,74HC157,
U3,DIP-14_W7.62mm_Socket_LongPads,1,74HC14,
U4,DIP-28_W15.24mm_Socket_LongPads,1,27512,
U5,DIP-14_W7.62mm_Socket_LongPads,1,74HC74,
U6,DIP-24_W7.62mm_Socket_LongPads,1,GAL22V10,

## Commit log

2024-08-11 C104
    Comiket 104
2024-08-11 Add C104 PDF
    Add C104 PDF
2024-08-11 Edit PDF
    EDIT PDF
2024-08-11 ADD RGB2HDMI profile
    ADD RGB2HDMI profile
2024-11-15 BUGFIX TRIG
    Bugfix TRIG polarity and adjust timing
